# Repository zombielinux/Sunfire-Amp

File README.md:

# Sunfire-Amp
This is an in progress reverse engineering of a Sunfire True Subwoofer MK2. The end goal is a faithful recreation of the amplifier with modern components through SPICE simulation.

Simulation will be ideally done in KiCAD, but may need to be done in LTSpice.

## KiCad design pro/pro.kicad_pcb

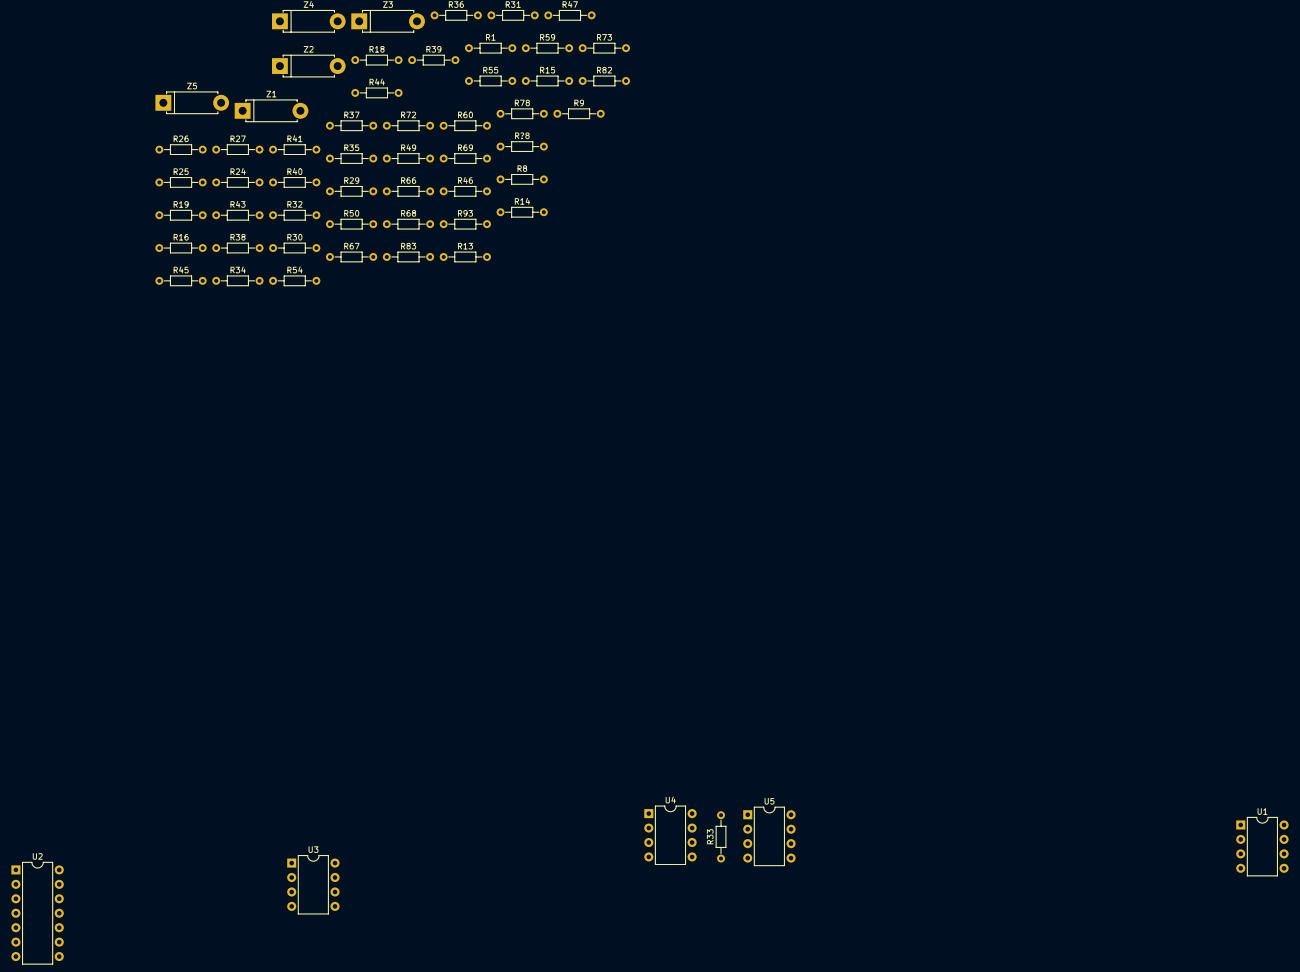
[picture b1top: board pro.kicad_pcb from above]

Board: 2 copper layers, 58 parts (0 on the bottom side), 40 nets, no tracks yet.

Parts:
R1, R8, R9, R13, R14, R15, R16, R18, R19, R24, R25, R26, R27, R29, R30, R31, R32, R33, R34, R35, R36, R37, R38, R39, R40, R41, R43, R44, R45, R46, R47, R49, R50, R54, R55, R59, R60, R66, R67, R68, R69, R72, R73, R78, R82, R83, R93: R; R_Axial_DIN0204_L3.6mm_D1.6mm_P7.62mm_Horizontal
R?8: R; R_Axial_DIN0204_L3.6mm_D1.6mm_P7.62mm_Horizontal
U1, U5: A2611; DIP-8_W7.62mm
U2: TL074; DIP-14_W7.62mm
U3, U4: BA10393; DIP-8_W7.62mm
Z1, Z2, Z3, Z4, Z5: D_Zener; D_5W_P10.16mm_Horizontal

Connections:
BIGNET1: R15.1, R29.1, R44.2, R45.2, R46.1, R55.2, R93.2
J1-Pin2: R38.2, R40.1, U3.2
J1-Pin3: R43.2, R59.2, R73.1, U2.4, Z4.1
unnamed: R1.1, R14.2
unnamed: R35.2, R36.2
unnamed: R19.1, R34.2, R47.2, Z2.1
unnamed: Z4.2, Z5.1
unnamed: R8.2, R59.1
unnamed: R60.2, R72.2
unnamed: R69.1, R78.2
unnamed: R73.2, R93.1
unnamed: R27.2, R30.2, R43.1
unnamed: R31.1, R44.1, R50.2
unnamed: R54.1, R67.2, R68.1
unnamed: U2.13, U2.14
Q2-Pin2: R14.1, R29.2
Q3-Pin3: R32.2, U4.3
Q4-Pin3: R33.1, R49.1
Q5-Pin2: R55.1, R69.2
Q7-Pin2: R47.1, U5.6
Q11-Pin2: R66.2, R83.1
Q11-Pin3: R16.2, R32.1, R60.1, R67.1, U3.4, U4.4, Z5.2
U1,5-Pin3: R18.1, U1.3, U4.7, U5.2, U5.3
U1-Pin5: U1.5, Z3.2
U1-Pin6: R35.1, U1.6
U1-Pin7: R36.1, U1.7, Z3.1
U2-Pin5: R37.1, R38.1, R39.1, U2.5
U2-Pin6: R40.2, U2.6
U2-Pin7: R9.2, R37.2, U2.7
U2-Pin8,9: U2.8, U2.9
U2-Pin10: R41.1, U2.10
U2-Pin11: R39.2, U2.11
U3,4-Pin8: R13.2, R18.2, R24.2, R33.2, U3.8, U4.8
U3-Pin1: R24.1, R41.2, U3.1
U3-Pin3,7: R13.1, R25.2, R26.2, U3.3, U3.7
U3-Pin5: R26.1, U3.5
U3-Pin6: R25.1, U3.6
U4-Pin2: R15.2, R16.1, U4.2
U5-Pin5: U5.5, Z1.2
U5-Pin7,8: R34.1, U5.7, U5.8, Z1.1

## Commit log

2019-10-17 Added Existing files
2019-10-17 Added Readme
